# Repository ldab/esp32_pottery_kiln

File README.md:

# kiln_controller
Connected electric kiln controller -> esp32, max31855, thermocouple type K, relay, contactor and energy meter. Including Kiln built plans.

## ESPHome firmware

An ESPHome configuration is available in [`esphome/kiln.yaml`](esphome/kiln.yaml). It targets the ESP32-WROOM-32 shown in the schematic and retains the four-stage ramp/hold firing schedule, 5 °C relay differential, 5.53 second contactor control cadence, controlled cooling, RGB status LED, and S0 energy pulse measurement using ESPHome's native `pulse_meter`. MQTT, Papertrail, and the old browser graph are not used by this configuration.

The ESPHome web server provides the firing profile number controls and Start, Stop, and Clear Fault buttons. Wi-Fi provisioning is handled by ESPHome's captive portal. It is a state control page; network credentials and firmware settings remain in the YAML/secrets file.

### Install

1. Copy `esphome/secrets.yaml.example` to `esphome/secrets.yaml` and replace its sample credentials. Generate a private API key with `openssl rand -base64 32`.
2. Install ESPHome 2026.9 or newer and run `esphome run esphome/kiln.yaml`.
3. After Wi-Fi setup, open `http://pottery-kiln.local/` or the ESP32's IP address. The HTTP page uses the username and password in `secrets.yaml`.
4. In the web page or Home Assistant, set all four target/rate/hold groups and press **Start Kiln Firing**. The target temperatures must be nondecreasing; the final target is limited to 1260 °C.

With no saved Wi-Fi credentials, connect to the `Kiln Fallback` access point and use its captive portal to configure the network. Profile parameters are saved as ESPHome number states. An interrupted or restarted firing does not resume automatically; the relay starts off and a new firing must be started manually.

### Hardware pins

| Schematic signal | ESP32 GPIO | ESPHome use |
| --- | ---: | --- |
| gRLY | 16 | Contactor relay output, active high, always off at boot |
| S0+ | 17 | Energy meter pulse input |
| MAX31855 CS | 22 | Thermocouple converter chip select |
| MAX31855 MISO/SO | 21 | Thermocouple converter data |
| MAX31855 SCK | 23 | Thermocouple converter clock |
| LED_R / LED_G / LED_B | 25 / 26 / 27 | Active-low RGB status indicator |

GPIO32/33 are the schematic's SDA/SCL connections and are not used by the current firmware. The energy calculation assumes the existing firmware's value of 0.5 Wh per S0 pulse.

### MAX31855 and high-temperature handling

The MAX31855K supports K-type measurements up to 1350 °C, so the project's 1260 °C profile limit is within its stated range. Although the schematic/BOM list L1/L2 ferrite beads, the assembled hardware has solder bridges at those positions; C7 (100 nF in the schematic) is also unpopulated. The MAX31855 inputs therefore have no added series ferrite or differential capacitor filtering, which can increase noise sensitivity. The original firmware's `Ignore SCG fault` behavior is retained by the small local ESPHome sensor component in `esphome/components/max31855_scg/`: it accepts a short-to-ground flag by itself, while an open thermocouple, short to VCC, or unreadable SPI data yields an invalid temperature and latches the heater off. This tolerance preserves the kiln workaround, but a real thermocouple short to ground can also make its reading unreliable. The 1300 °C firmware cutoff is a software limit and does not replace an independent kiln over-temperature cutout.

### Remote crash reporting

ESPHome's native API logger automatically retains warm-reset crash backtraces and reports them after the device reconnects. ESPHome CLI/Device Builder can decode the trace with the debug symbols from the matching firmware build. The configuration also exposes the last reset reason to Home Assistant and sends `esphome.kiln_crash` after panic, watchdog, brownout, or CPU lock-up resets. In the ESPHome integration settings, allow this device to perform Home Assistant actions. Then add [`home-assistant-crash-automation.yaml`](esphome/home-assistant-crash-automation.yaml) to send a persistent notification. See [ESPHome crash troubleshooting](https://esphome.io/guides/troubleshooting/) and the [MAX31855 component](https://esphome.io/components/sensor/max31855/).

 ## TODO

- [ ] Temperature Ramp rate monitor;
- [ ] Cooling monitor;
- [ ] Cool upload progress: https://codepen.io/takaneichinose/pen/jOWXBBd

## VOID

"Lorem ipsum dolor sit amet, consectetur adipiscing elit, sed do eiusmod tempor incididunt ut labore et dolore magna aliqua. Ut enim ad minim veniam, quis nostrud exercitation ullamco laboris nisi ut aliquip ex ea commodo consequat. Duis aute irure dolor in reprehenderit in voluptate velit esse cillum dolore eu fugiat nulla pariatur. Excepteur sint occaecat cupidatat non proident, sunt in culpa qui officia deserunt mollit anim id est laborum."

## Bil of materials

Description | Price
------------ | -------------
[4x Modules enclosure](https://www.amazon.de/gp/product/B07K5X5KZQ/ref=ppx_yo_dt_b_asin_title_o00_s00?ie=UTF8&psc=1) | €8.00
[Energy meter with S0 output](https://www.amazon.de/gp/product/B083H7NT2R/ref=ppx_yo_dt_b_asin_title_o00_s01?ie=UTF8&psc=1) | €13.00
[HDR-15 Power Supply](https://www.amazon.de/gp/product/B06XWQSJGW/ref=ppx_yo_dt_b_asin_title_o00_s00?ie=UTF8&psc=1) | €13.00
[12v/16A Relay](https://www.tme.eu/se/en/details/pi85012dc00ld/electromagnetic-relays-sets/relpol/pi85-012dc-00ld/) | €13.00
esp32 | €5.00
max31855 | €10.00
[Type-K thermocouple](https://www.keramik-kraft.com/en/Kiln-Building--Repair/Pyrometry/Thermocouple-Nickel-Typ-K/Thermocouple-Type-K-open-with-flange-l-12cm.html?sel=13) | €50.00
Cables, terminals, etc | €10.00

Total: **€120.00**

## Element calculations

### Element power

* This is determined by the power outlet, i.e `230Vac@16A` -> **3680W**

* Some [resources](https://knifedogs.com/threads/heat-treat-oven-how-to-design-and-calculate-the-heating-elements.21072/) indicate 0.6 - 1.3 W/cm2 of wall -> `Aw = (30.4 * 30.4 * 2) + (30.4 * 34.2 * 4) = 6,007.04 cm2` therefore Element should be between *3604W* and *7800W*.

* [KMT-614](https://skutt.com/products-page/ceramic-kilns/kmt-614/) and [Ecotop 20](https://www.rohde.eu/en/arts-and-crafts/products/toploaders/ecotop-series/ecotop-20) are both ~20L with 2300W element and rated to [Cone 6](https://www.ortonceramic.com/files/2676/File/orton-cone-chart-2016.pdf), aka ~1260°C

### Element size

Using Kanthal D - Other variants were hard to find, Kanthal D can be bought at [eveks.se](https://eveks.se/kategorier/461-kanthal-tr%C3%A5d-01-5mm-v%C3%A4rmekabel-14765-kanthal-d-motst%C3%A5ndstr%C3%A5d-1-100-meter-4066435006815.html)

* 1.6mm -> R = 0.67 Ohms/m
* L = ( 3680 / 16^2 ) / 0.67 = **~21.5m**

### Surface Load

* Accordingly to Kanthal [datasheet](./extras/Kanthal%20handbook.pdf), kiln application should have a Surface Load between 3-9 W/cm2:

`3680 / (2pi x 0.08 x 2150) = **3.4**W/cm2`

* [furnace handbook](./extras/file1359965681_U3423.pdf) page 7 indicates max 2.4W/cm2 @ 1100°C

### Coil Diameter

* In order to avoid deformation on horizontal coils, the coild diameter should stay below 10mm accordingly to:

* Therefore let's use a **M8** rod to coil the wire.

### Coil Length

* The internal element perimeter is ~1216mm, if 3x turns are planned, we end up with a **3648mm** coil;

### Coil Pitch

*Coil pitch is normally 2-4 times the wire diameter* [page_79](./extras/Kanthal20handbook.pdf) -> aka 2-4mm

`s = (11.2 - 8) x pi / sqrt((21500 / 3648) ^ 2 - 1) = ~**2mm**`

## Bricks

The kils was build with [JM23](https://www.morganthermalceramics.com/media/4120/ifb-insulation-range-1100-1315-english.pdf) bricks

### Bricks thermal heat loss

## PCB

PCB layout and files are found at  open it with KiCad

## Known Limitations

* 

## Credits

Github Shields and Badges created with [Shields.io](https://github.com/badges/shields/)

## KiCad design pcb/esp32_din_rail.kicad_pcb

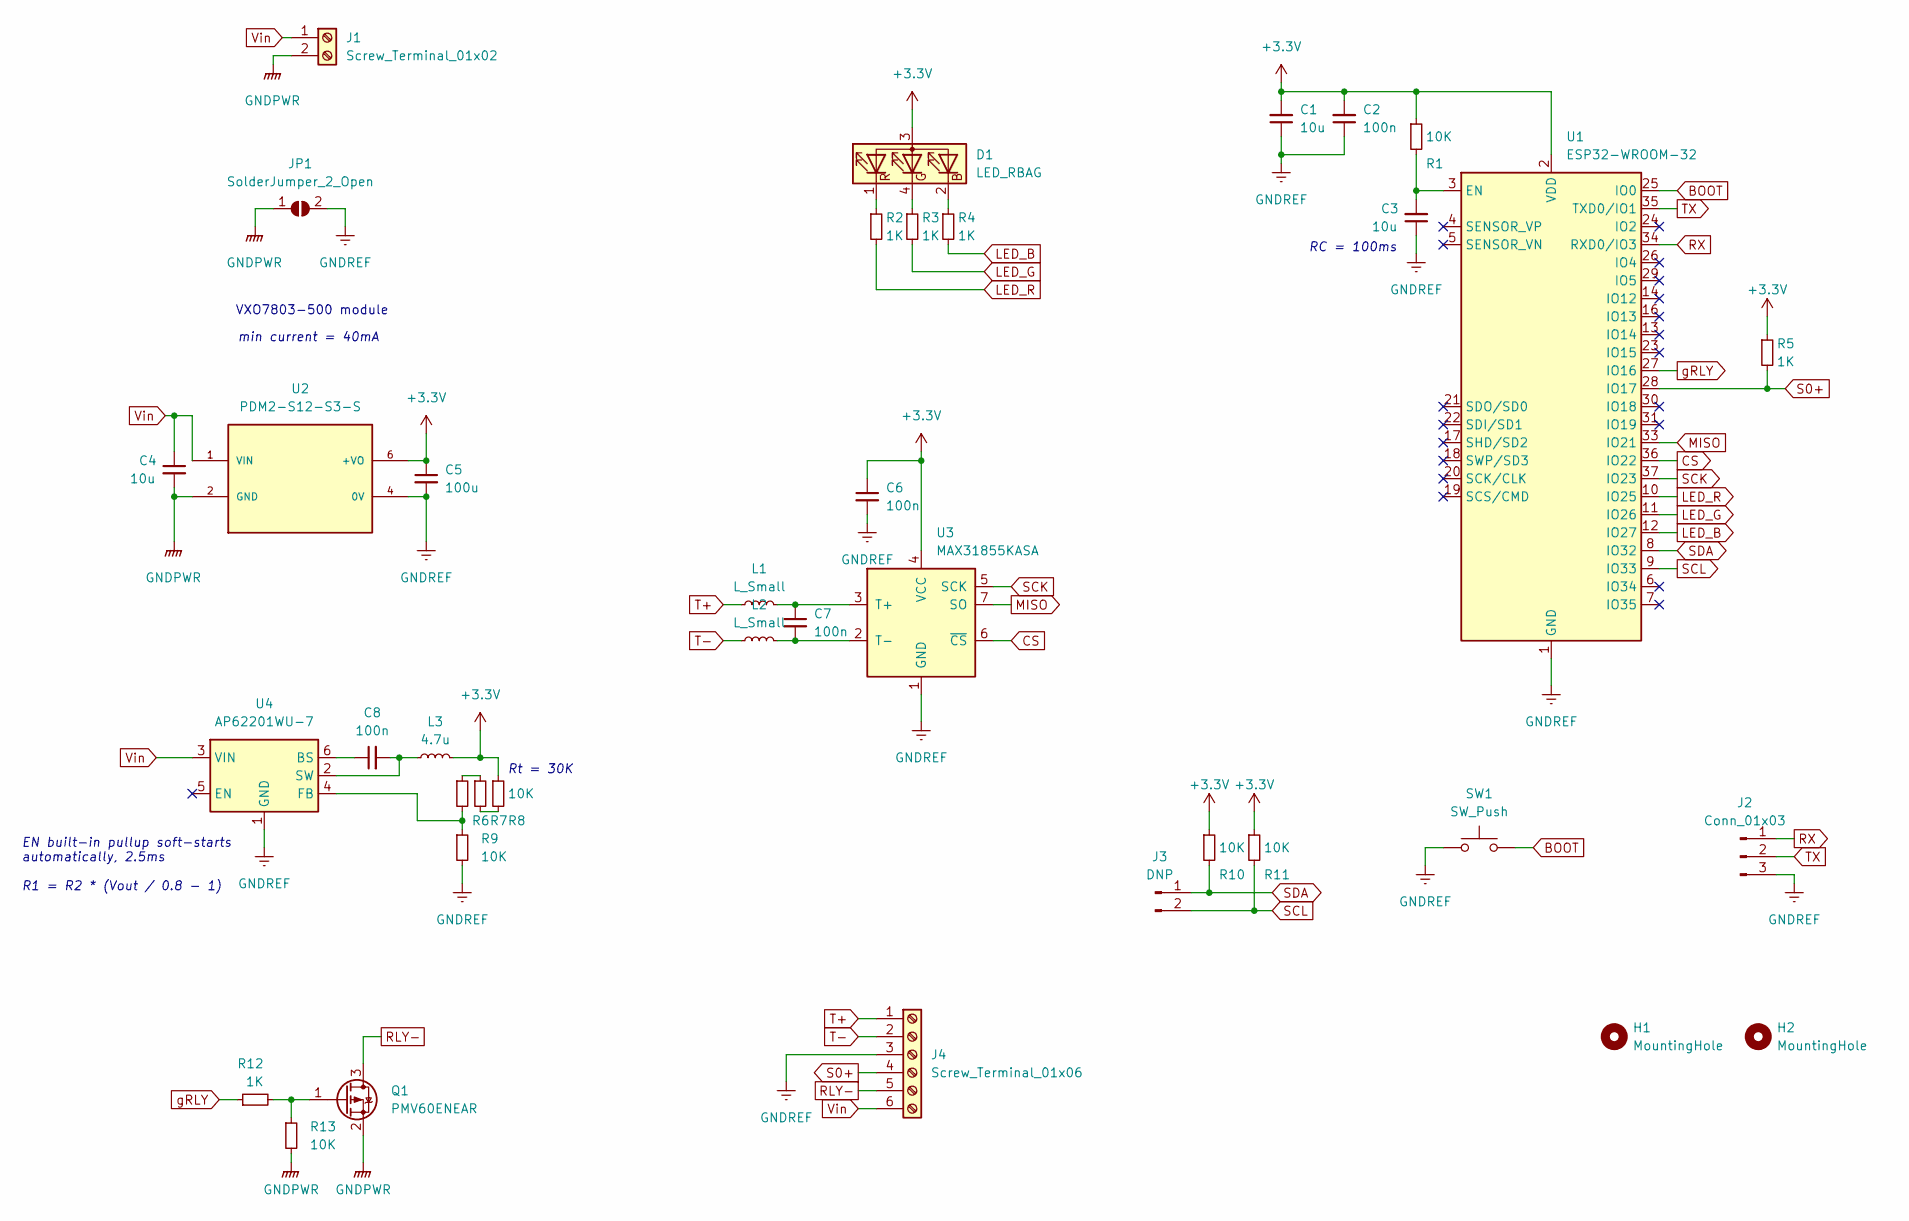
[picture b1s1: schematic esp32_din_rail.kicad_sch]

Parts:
C1, C3, C4: 10u; C_0603_1608Metric
C2, C6, C7, C8: 100n; C_0603_1608Metric
C5: 100u; C_1206_3216Metric; LCSC C77085
D1: LED_RBAG; LED_Cree-PLCC4_2x2mm_CW; LCSC C108793
H1, H2: MountingHole; MountingHole_2.7mm_M2.5
J1: Screw_Terminal_01x02; TerminalBlock_RND_205-00067_1x02_P7.50mm_Horizontal; Mouser 691216910002
J2: Conn_01x03; PinHeader_1x03_P2.54mm_Vertical
J3: DNP; PinHeader_1x02_P2.54mm_Vertical
J4: Screw_Terminal_01x06; TerminalBlock_Phoenix_PT-1,5-6-5.0-H_1x06_P5.00mm_Horizontal; Mouser 1935200
JP1: SolderJumper_2_Open; SolderJumper-2_P1.3mm_Open_RoundedPad1.0x1.5mm
L1, L2: L_Small; L_0402_1005Metric
L3: 4.7u; L_1210_3225Metric
Q1: PMV60ENEAR; SOT-23; Mouser 771-PMV60ENEAR
R1, R6, R7, R8, R9, R10, R11, R13: 10K; R_0603_1608Metric
R2, R3, R4, R5, R12: 1K; R_0603_1608Metric; LCSC C384295
SW1: SW_Push; SW_PUSH_6mm
U1: ESP32-WROOM-32
U2: PDM2-S12-S3-S; CONV_PDM2-S12-S3-S; PARTREV 1.03
U3: MAX31855KASA; SOIC-8_3.9x4.9mm_P1.27mm
U4: AP62201WU-7; SOT-23-6

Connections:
+3V3: C1.2, C2.2, C5.1, C6.1, D1.3 (A), L3.2, R1.1, R5.1, R8.1, R10.1, R11.1, U1.2 (VDD), U2.6 (+VO), U3.4 (VCC)
BOOT: SW1.2, U1.25 (IO0)
CS: U1.36 (IO22), U3.6 (~CS)
GNDPWR: C4.2, J1.2, JP1.1 (A), Q1.2 (S), R13.2, U2.2 (GND)
GNDREF: C1.1, C2.1, C3.1, C5.2, C6.2, J2.3, J4.3, JP1.2 (B), R9.2, SW1.1, U1.1 (GND), U1.15 (GND), U1.38 (GND), U1.39 (GND), U2.4 (0V), U3.1 (GND), U4.1 (GND)
LED_B: R4.2, U1.12 (IO27)
LED_G: R3.2, U1.11 (IO26)
LED_R: R2.2, U1.10 (IO25)
MISO: U1.33 (IO21), U3.7 (SO)
unnamed: C3.2, R1.2, U1.3 (EN)
unnamed: C7.1, L1.2, U3.3 (T+)
unnamed: C7.2, L2.2, U3.2 (T-)
unnamed: C8.1, U4.6 (BS)
unnamed: C8.2, L3.1, U4.2 (SW)
unnamed: D1.1 (RK), R2.1
unnamed: D1.2 (BK), R4.1
unnamed: D1.4 (GK), R3.1
unnamed: Q1.1 (G), R12.2, R13.1
unnamed: R6.1, R7.1
unnamed: R6.2, R9.1, U4.4 (FB)
unnamed: R7.2, R8.2
RLY-: J4.5, Q1.3 (D)
RX: J2.1, U1.34 (RXD0/IO3)
S0+: J4.4, R5.2, U1.28 (IO17)
SCK: U1.37 (IO23), U3.5 (SCK)
SCL: J3.2, R11.2, U1.9 (IO33)
SDA: J3.1, R10.2, U1.8 (IO32)
T+: J4.1, L1.1
T-: J4.2, L2.1
TX: J2.2, U1.35 (TXD0/IO1)
Vin: C4.1, J1.1, J4.6, U2.1 (VIN), U4.3 (VIN)
gRLY: R12.1, U1.27 (IO16)

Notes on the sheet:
Rt = 30K
VXO7803-500 module
RC = 100ms
EN built-in pullup soft-starts automatically, 2.5ms R1 = R2 * (Vout / 0.8 - 1)
min current = 40mA

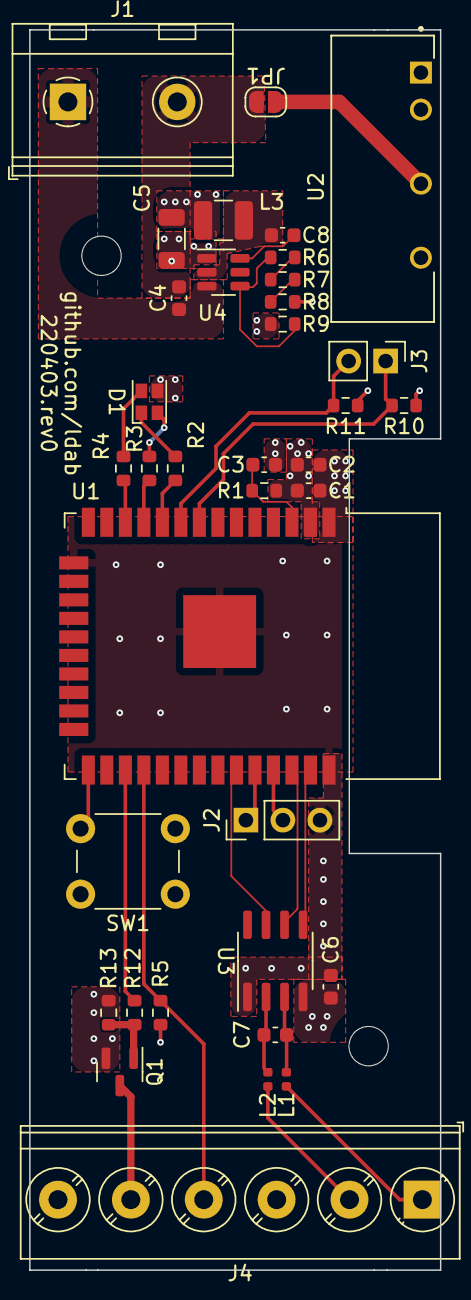
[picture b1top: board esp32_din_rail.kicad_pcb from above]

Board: 4 copper layers, 28.2 x 85.1 mm, 38 parts (0 on the bottom side), 32 nets.

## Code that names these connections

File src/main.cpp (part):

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// https://randomnerdtutorials.com/esp8266-pinout-reference-gpios/
#define RELAY        16
#define POWER        17
#define LED_R        25
#define LED_G        26
#define LED_B        27
#define SPI_CS       22
#define SPI_MISO     21
#define SPI_CLK      23
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  pinMode(RELAY, OUTPUT);
  digitalWrite(RELAY, LOW);

  pinMode(LED_R, OUTPUT);
  pinMode(LED_G, OUTPUT);
  pinMode(LED_B, OUTPUT);
  ledOff();
}

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
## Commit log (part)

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2022-01-03 release
2022-01-03 Squashed commit of the following:
    commit eec104c16eb9b150623a43495655bbd0db684e37
    Author: ldab <l.bispo@live.com>
    Date: Sun Jan 2 20:43:48 2022 +0100
    temp differential
    commit 90ddbac9a1403a6511b5b3fb145a5e8f4b0a8779
    Author: ldab <l.bispo@live.com>
2022-01-03 get RSSI V51
2022-01-03 code format
2022-01-07 update IDF and Libs
2022-01-10 initial test
2022-01-16 safety check timer timeout
    avoid wrongly no current alarm when is off for longer period.
2022-01-19 My pid
2022-01-20 include paperTrail
2022-01-20 revert to on_off
2022-01-20 burst fire 10sec, 10steps resolution
2022-01-20 burst period 1.4sec to correctly measure current
2022-01-21 glaze fire 4 cups
2022-03-08 stop sending variables as String
2022-03-08 versioning and templateID
2022-03-08 disable slow cooling
2022-03-08 change notify
2022-03-09 remove Time input and paperlog
2022-03-09 wait currentST sync
2022-03-13 Blynk 2.0 (#3)
    * stop sending variables as String
    * versioning and templateID
    * disable slow cooling
    * change notify
    * remove Time input and paperlog
    * wait currentST sync
2022-03-13 untested
2022-03-13 sync step from cloud
2022-03-14 bump version / remove log
2022-03-14 papertrail
2022-03-14 publish reset reason to papertrail (#4)
    * sync step from cloud
    * bump version / remove log
    * papertrail
2022-03-14 use blynk to OTA
2022-03-14 use blynk to OTA (#5)
2022-03-14 Alarm and Notification Flags
    limit the number of notifications
2022-03-17 fix crash but does not load from cloud, line 129
    faster sync
2022-03-17 workflow
2022-03-17 folder
2022-03-17 badges
2022-03-17 badges fix
2022-03-17 keep elf for debbuging
2022-03-17 Implement CI on GitHub Actions (#6)
    * add secrets.h
    * keep *.elf for debugging
2022-03-17 recover data from cloud upon watchdog
2022-04-04 import html
2022-04-04 compatibility esp32
2022-04-04 porting
2022-04-04 mqtt
2022-04-05 mqtt publish-work
2022-04-05 fire param
2022-04-06 include graph
2022-04-06 /info page
2022-04-06 plot real time
2022-04-07 plot saved graph, crash at 100 readings
2022-04-07 send data to graph, pthread
2022-04-08 send graph data when page loads
2022-04-08 fix surface load
2022-04-09 store data with time, also graphSend
2022-04-09 fix html error and size
2022-04-10 DBG tidy up
2022-04-10 status display on index
2022-04-10 fix crash on portal
2022-04-11 notify
2022-04-11 replace blynk.log
2022-04-11 papertrail printf
2022-04-11 clean update
2022-04-25 espressif32@3.5.0 checkout
2022-04-25 todo button off
2022-04-25 send temperature and fix interval
2022-04-25 restart safety timer
2022-04-25 clean up
2022-04-25 clear warnings
2022-04-25 recover crash from SPIFFS
2022-04-25 send power to index
2022-04-26 print RSSI on info
2022-04-27 move to esp32 - dry run (#7)
    * import html
    * PCB
    * compatibility esp32
    * porting
    * mqtt
    * mqtt publish-work
2022-04-27 port arduino 2.0.0
2022-04-30 reset button
2022-04-30 fix time to load graph
2022-04-30 led colors
2022-04-30 fix interrupt, no float on ISR
2022-04-30 Arduino 200 (#8)
    * port arduino 2.0.0
    * reset button
    * fix time to load graph
    * led colors
    * fix interrupt, no float on ISR
2022-05-02 fix wrong R5/R12 silk screen
2022-05-03 update readme with new kiln
2022-06-15 fix step recover after crash
2022-12-28 allow re-configuration
2022-12-28 allow re-configuration (#9)

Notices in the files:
README.md:
License: MIT
